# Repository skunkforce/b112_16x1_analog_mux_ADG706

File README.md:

# edgy_board number b112
This design is part of the [edgy board project](https://github.com/skunkforce/edgy_boards). 

# getting started
This repository uses submodules. After cloning use the command 

```$ git submodule update --init --recursive```

to pull the submodules before opening the project with kicad. 

# Tests
Tests can be found in [TESTS.md](TESTS.md)

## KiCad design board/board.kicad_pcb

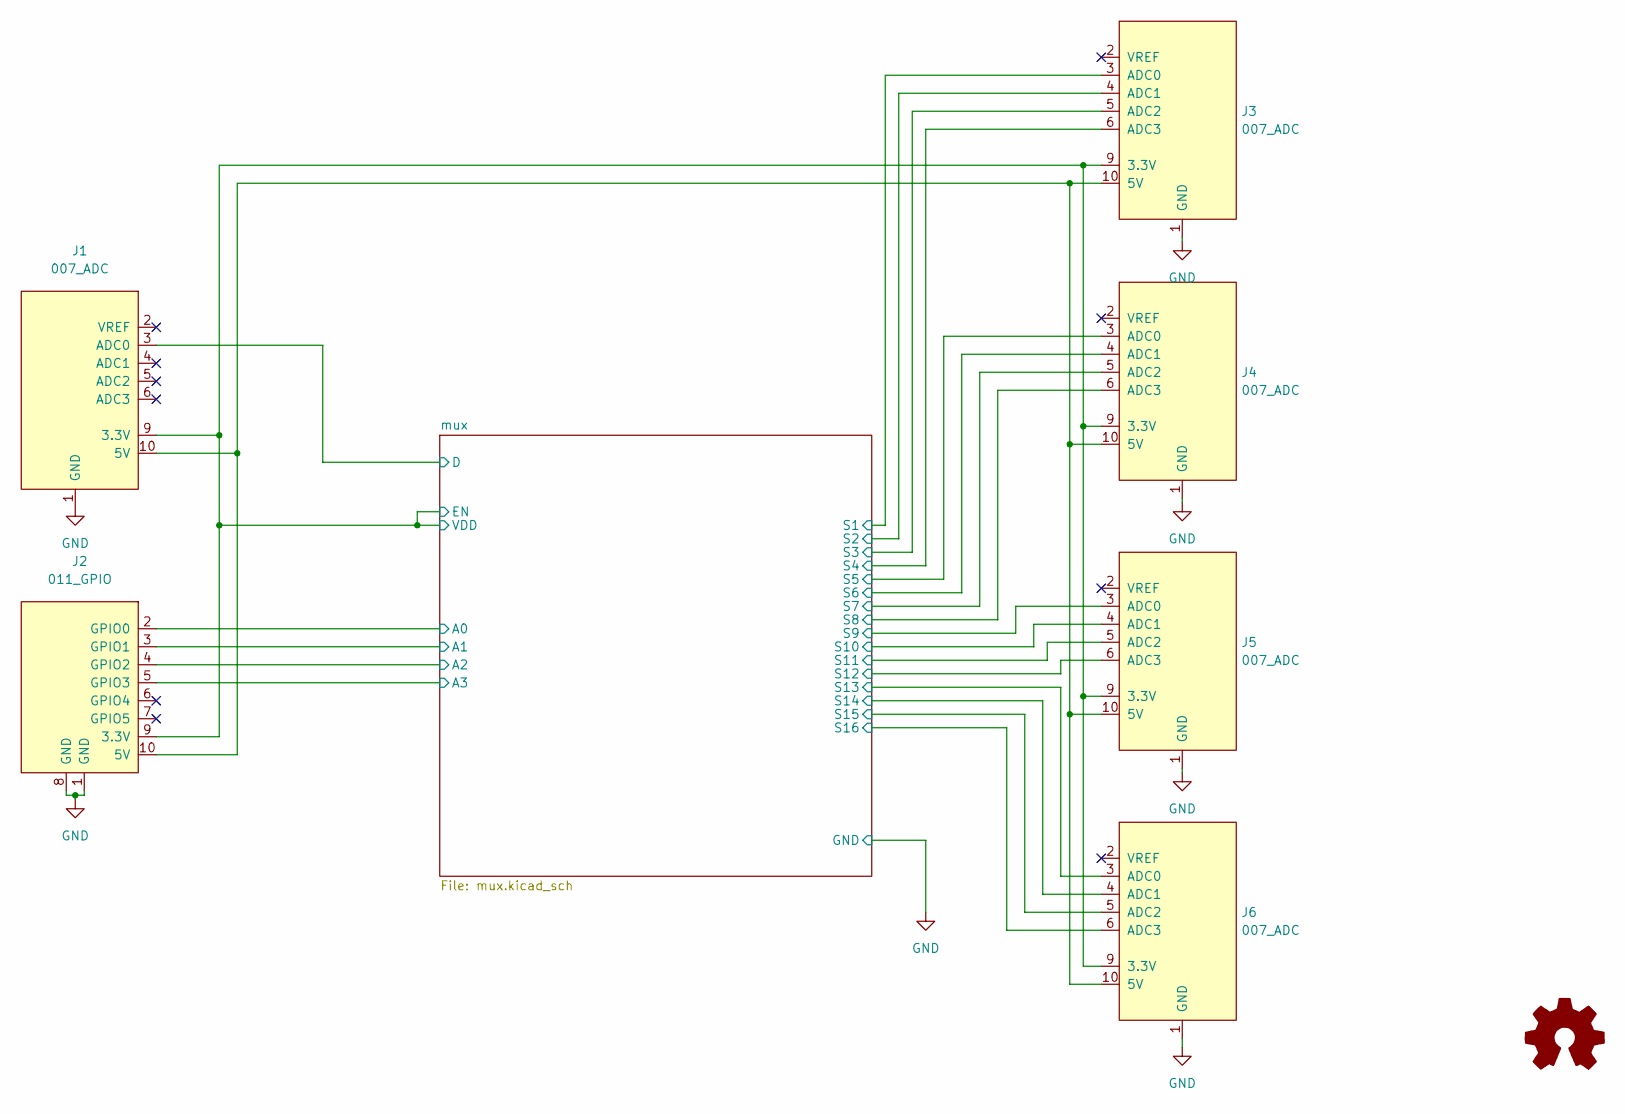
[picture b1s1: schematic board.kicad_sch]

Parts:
J1: 007_ADC; on_edge_2x05_device
J2: 011_GPIO; on_edge_2x05_device
J3, J4, J5, J6: 007_ADC; on_edge_2x05_host
LOGO1: Logo_Open_Hardware_Small; OSHW-Symbol_6.7x6mm_SilkScreen

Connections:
/mux/A0: J2.2 (GPIO0); also elsewhere on the board
/mux/A1: J2.3 (GPIO1); also elsewhere on the board
/mux/A2: J2.4 (GPIO2); also elsewhere on the board
/mux/A3: J2.5 (GPIO3); also elsewhere on the board
/mux/D: J1.3 (ADC0); also elsewhere on the board
/mux/EN: J1.9 (3.3V), J2.9 (3.3V), J3.9 (3.3V), J4.9 (3.3V), J5.9 (3.3V), J6.9 (3.3V); also elsewhere on the board
/mux/S1: J3.3 (ADC0); also elsewhere on the board
/mux/S2: J3.4 (ADC1); also elsewhere on the board
/mux/S3: J3.5 (ADC2); also elsewhere on the board
/mux/S4: J3.6 (ADC3); also elsewhere on the board
/mux/S5: J4.3 (ADC0); also elsewhere on the board
/mux/S6: J4.4 (ADC1); also elsewhere on the board
/mux/S7: J4.5 (ADC2); also elsewhere on the board
/mux/S8: J4.6 (ADC3); also elsewhere on the board
/mux/S9: J5.3 (ADC0); also elsewhere on the board
/mux/S10: J5.4 (ADC1); also elsewhere on the board
/mux/S11: J5.5 (ADC2); also elsewhere on the board
/mux/S12: J5.6 (ADC3); also elsewhere on the board
/mux/S13: J6.3 (ADC0); also elsewhere on the board
/mux/S14: J6.4 (ADC1); also elsewhere on the board
/mux/S15: J6.5 (ADC2); also elsewhere on the board
/mux/S16: J6.6 (ADC3); also elsewhere on the board
GND: J1.1 (GND), J2.1 (GND), J2.8 (GND), J3.1 (GND), J4.1 (GND), J5.1 (GND), J6.1 (GND); also elsewhere on the board
unnamed: J1.10 (5V), J2.10 (5V), J3.10 (5V), J4.10 (5V), J5.10 (5V), J6.10 (5V)

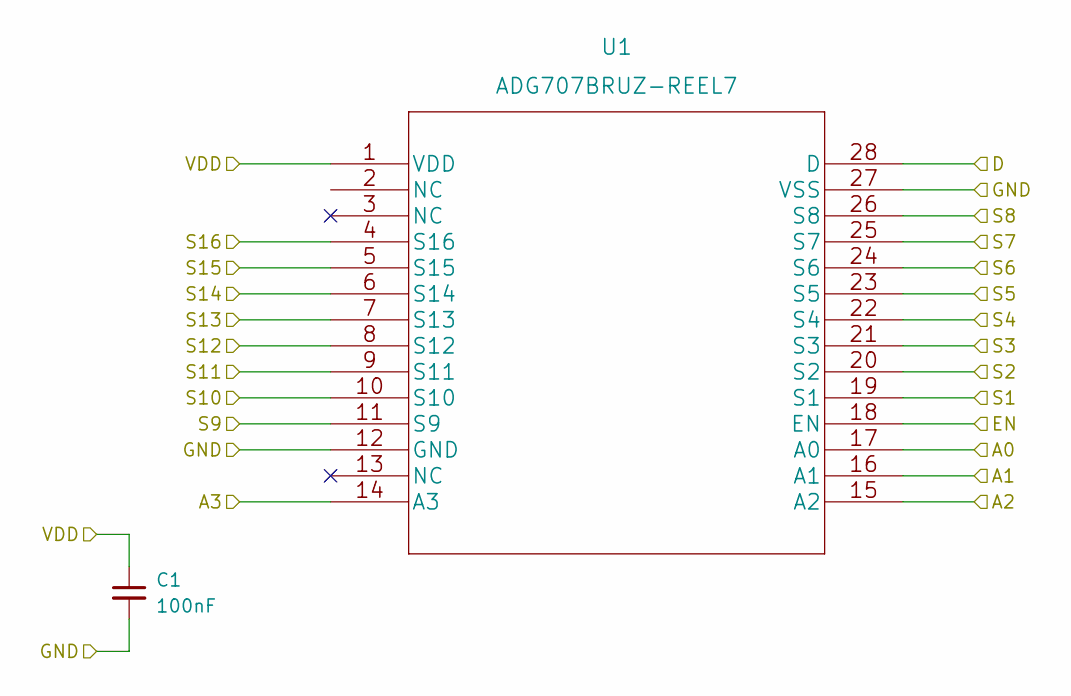
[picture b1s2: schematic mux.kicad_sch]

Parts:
C1: 100nF; C_0603_1608Metric
U1: ADG707BRUZ-REEL7

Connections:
/mux/A0: U1.17 (A0); also elsewhere on the board
/mux/A1: U1.16 (A1); also elsewhere on the board
/mux/A2: U1.15 (A2); also elsewhere on the board
/mux/A3: U1.14 (A3); also elsewhere on the board
/mux/D: U1.28 (D); also elsewhere on the board
/mux/EN: C1.1, U1.1 (VDD), U1.18 (EN); also elsewhere on the board
/mux/S1: U1.19 (S1); also elsewhere on the board
/mux/S2: U1.20 (S2); also elsewhere on the board
/mux/S3: U1.21 (S3); also elsewhere on the board
/mux/S4: U1.22 (S4); also elsewhere on the board
/mux/S5: U1.23 (S5); also elsewhere on the board
/mux/S6: U1.24 (S6); also elsewhere on the board
/mux/S7: U1.25 (S7); also elsewhere on the board
/mux/S8: U1.26 (S8); also elsewhere on the board
/mux/S9: U1.11 (S9); also elsewhere on the board
/mux/S10: U1.10 (S10); also elsewhere on the board
/mux/S11: U1.9 (S11); also elsewhere on the board
/mux/S12: U1.8 (S12); also elsewhere on the board
/mux/S13: U1.7 (S13); also elsewhere on the board
/mux/S14: U1.6 (S14); also elsewhere on the board
/mux/S15: U1.5 (S15); also elsewhere on the board
/mux/S16: U1.4 (S16); also elsewhere on the board
GND: C1.2, U1.12 (GND), U1.27 (VSS); also elsewhere on the board

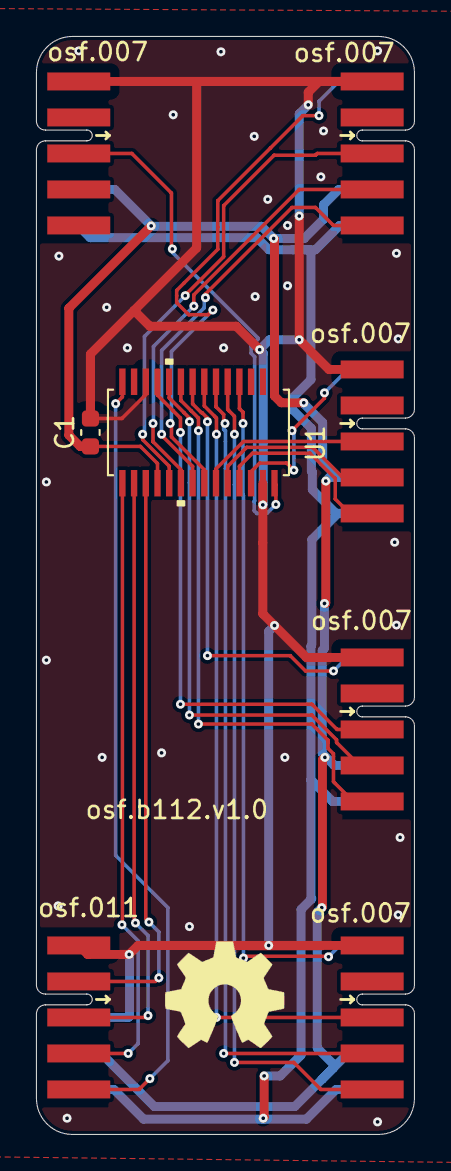
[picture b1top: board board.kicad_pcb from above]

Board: 2 copper layers, 21.0 x 61.0 mm, 9 parts (0 on the bottom side), 24 nets.

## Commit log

2023-03-15 initial
2023-03-31 fixed part number and added 3D model
